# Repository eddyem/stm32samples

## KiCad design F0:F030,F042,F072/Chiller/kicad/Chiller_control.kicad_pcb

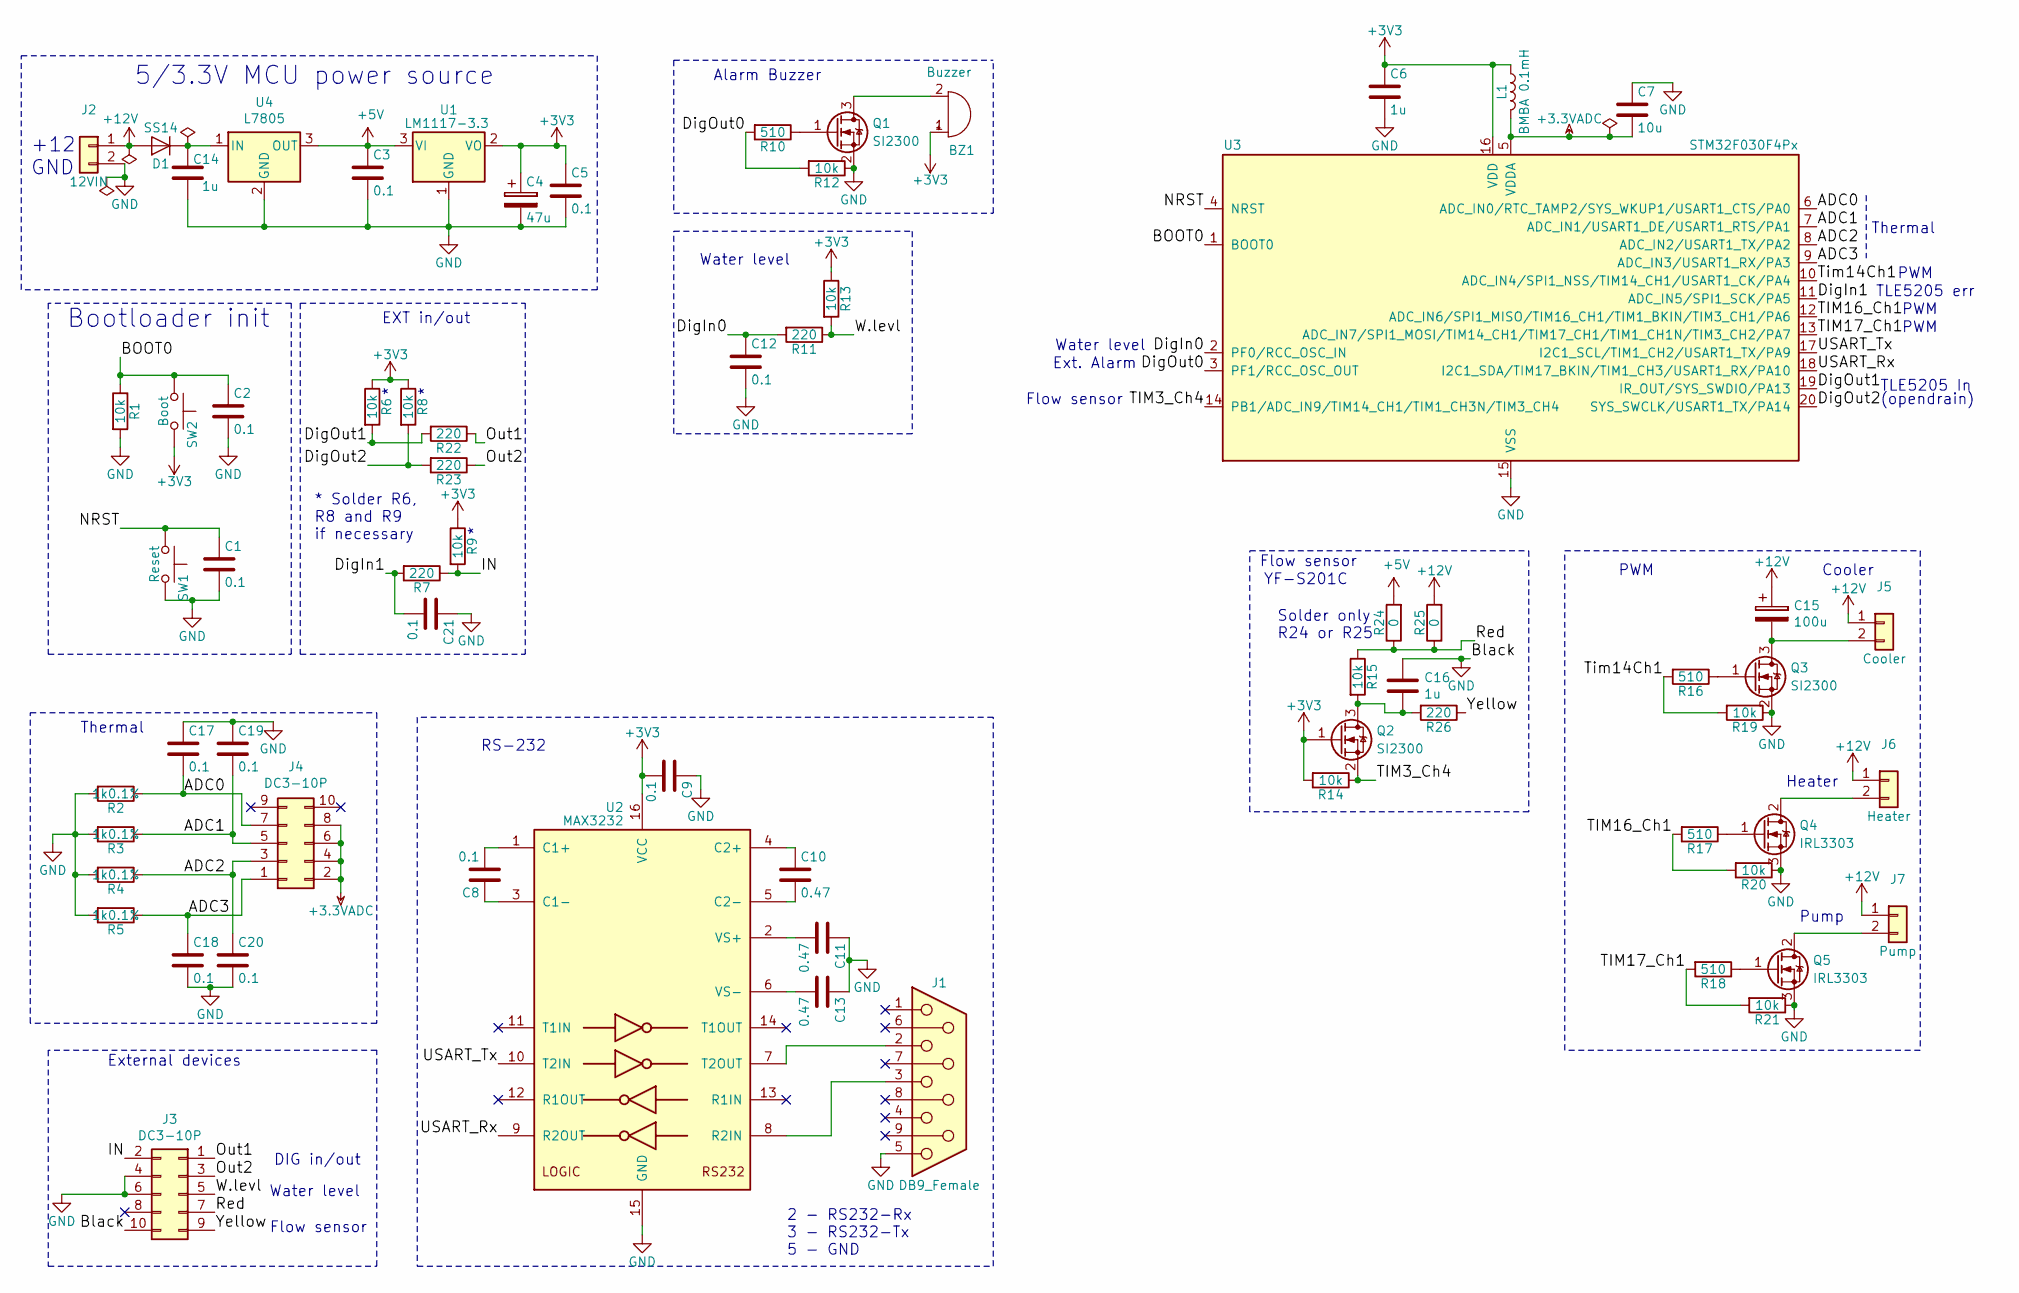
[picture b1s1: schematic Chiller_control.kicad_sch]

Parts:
BZ1: Buzzer; Buzzer_12x9.5RM7.6
C1, C2, C3, C5, C8, C9, C12, C17, C18, C19, C20, C21: 0.1; C_0603_1608Metric_Pad0.99x1.00mm_HandSolder
C4: 47u; CP_Tantalum_Case-A_EIA-3216-18_Hand
C6: 1u; C_0805_HandSoldering
C7: 10u; C_1206_HandSoldering
C10, C11, C13: 0.47; C_0805_HandSoldering
C14, C16: 1u; C_0805_2012Metric_Pad1.29x1.40mm_HandSolder
C15: 100u; CP_Radial_D8.0mm_P3.50mm
D1: SS14; D_SMA_Handsoldering
J1: DB9_Female; DB9-F
J2: 12VIN; TerminalBlock_Pheonix_MKDS1.5-2pol
J3, J4: DC3-10P; IDC-Header_2x05_P2.54mm_Vertical
J5: Cooler; TerminalBlock_Pheonix_MKDS1.5-2pol
J6: Heater; TerminalBlock_Pheonix_MKDS1.5-2pol
J7: Pump; TerminalBlock_Pheonix_MKDS1.5-2pol
L1: BMBA 0.1mH; R_0805_HandSoldering
Q1, Q2, Q3: SI2300; SOT-23_Handsoldering
Q4, Q5: IRL3303; TO-220-3_Vertical
R1, R6, R8, R9, R12, R13, R14, R15, R19, R20, R21: 10k; R_0603_HandSoldering
R2, R3, R4, R5: 1k0.1%; R_0805_HandSoldering
R7, R22, R23, R26: 220; R_0805_2012Metric_Pad1.29x1.40mm_HandSolder
R10, R16, R17, R18: 510; R_0603_HandSoldering
R11: 220; R_0805_HandSoldering
R24, R25: 0; R_0805_2012Metric_Pad1.29x1.40mm_HandSolder
SW1: Reset; SW_SPST_FSMSM
SW2: Boot; SW_SPST_FSMSM
U1: LM1117-3.3; SOT-223
U2: MAX3232; SOIC-16_3.9x9.9mm_Pitch1.27mm
U3: STM32F030F4Px; TSSOP-20_4.4x6.5mm_Pitch0.65mm
U4: L7805; TO-220-3_Vertical

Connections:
+3.3VADC: C7.2, J4.2, J4.4, J4.6, J4.8, L1.2, U3.5 (VDDA)
+3V3: BZ1.1 (+), C4.1, C5.1, C6.1, C9.2, L1.1, Q2.1 (G), R6.1, R8.1, R9.1, R13.1, R14.2, SW2.2, U1.2 (VO), U2.16 (VCC), U3.16 (VDD)
+5V: C3.1, R24.2, U1.3 (VI), U4.3 (OUT)
+12V: C15.1, D1.2 (A), J2.1, J5.1, J6.1, J7.1, R25.2
/ADC0: C17.2, J4.7, R2.1, U3.6 (ADC_IN0/RTC_TAMP2/SYS_WKUP1/USART1_CTS/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)
/ADC1: C19.2, J4.5, R3.1, U3.7 (ADC_IN1/USART1_DE/USART1_RTS/PA1)
/ADC2: C20.1, J4.3, R4.1, U3.8 (ADC_IN2/USART1_TX/PA2)
/ADC3: C18.1, J4.1, R5.1, U3.9 (ADC_IN3/USART1_RX/PA3)
/BOOT0: C2.1, R1.1, SW2.1, U3.1 (BOOT0)
/DigIn0: C12.1, R11.2, U3.2 (PF0/RCC_OSC_IN)
/DigIn1: C21.2, R7.2, U3.11 (ADC_IN5/SPI1_SCK/PA5)
/DigOut0: R10.2, R12.2, U3.3 (PF1/RCC_OSC_OUT)
/DigOut1: R6.2, R22.2, U3.19 (IR_OUT/SYS_SWDIO/PA13)
/DigOut2: R8.2, R23.2, U3.20 (SYS_SWCLK/USART1_TX/PA14)
/IN: J3.2, R7.1, R9.2
/NRST: C1.1, SW1.1, U3.4 (NRST)
/Out1: J3.1, R22.1
/Out2: J3.3, R23.1
/Red: J3.7, R15.1, R24.1, R25.1
/TIM3_Ch4: Q2.2 (S), R14.1, U3.14 (PB1/ADC_IN9/TIM14_CH1/TIM1_CH3N/TIM3_CH4)
/TIM16_Ch1: R17.2, R20.2, U3.12 (ADC_IN6/SPI1_MISO/TIM16_CH1/TIM1_BKIN/T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)
/TIM17_Ch1: R18.2, R21.2, U3.13 (ADC_IN7/SPI1_MOSI/TIM14_CH1/TIM17_CH1/T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)
/Tim14Ch1: R16.2, R19.2, U3.10 (ADC_IN4/SPI1_NSS/TIM14_CH1/USART1_CK/PA4)
/USART_Rx: U2.9 (R2OUT), U3.18 (I2C1_SDA/TIM17_BKIN/TIM1_CH3/USART1_RX/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)
/USART_Tx: U2.10 (T2IN), U3.17 (I2C1_SCL/TIM1_CH2/USART1_TX/PA9)
/W.levl: J3.5, R11.1, R13.2
/Yellow: J3.9, R26.1
GND: C1.2, C2.2, C3.2, C4.2, C5.2, C6.2, C7.1, C9.1, C11.1, C12.2, C13.1, C14.2, C16.1, C17.1, C18.2, C19.1, C20.2, C21.1, J1.5, J2.2, J3.4, J3.6, J3.10, Q1.2 (S), Q3.2 (S), Q4.3 (S), Q5.3 (S), R1.2, R2.2, R3.2, R4.2, R5.2, R12.1, R19.1, R20.1, R21.1, SW1.2, U1.1 (GND), U2.15 (GND), U3.15 (VSS), U4.2 (GND)
unnamed: BZ1.2 (-), Q1.3 (D)
unnamed: C8.1, U2.3 (C1-)
unnamed: C8.2, U2.1 (C1+)
unnamed: C10.1, U2.4 (C2+)
unnamed: C10.2, U2.5 (C2-)
unnamed: C11.2, U2.2 (VS+)
unnamed: C13.2, U2.6 (VS-)
unnamed: C14.1, D1.1 (K), U4.1 (IN)
unnamed: C15.2, J5.2, Q3.3 (D)
unnamed: C16.2, Q2.3 (D), R15.2, R26.2
unnamed: J1.2, U2.7 (T2OUT)
unnamed: J1.3, U2.8 (R2IN)
unnamed: J6.2, Q4.2 (D)
unnamed: J7.2, Q5.2 (D)
unnamed: Q1.1 (G), R10.1
unnamed: Q3.1 (G), R16.1
unnamed: Q4.1 (G), R17.1
unnamed: Q5.1 (G), R18.1

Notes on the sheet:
Thermal
Solder only R24 or R25
Alarm Buzzer
Water level
PWM
+12 GND
Ext. Alarm
Bootloader init
RS-232
EXT in/out
5/3.3V MCU power source
* Solder R6, R8 and R9 if necessary
Cooler
Flow sensor
(opendrain)
DIG in/out
External devices
TLE5205 In
Pump
TLE5205 err
2 - RS232-Rx 3 - RS232-Tx 5 - GND
YF-S201C
Heater

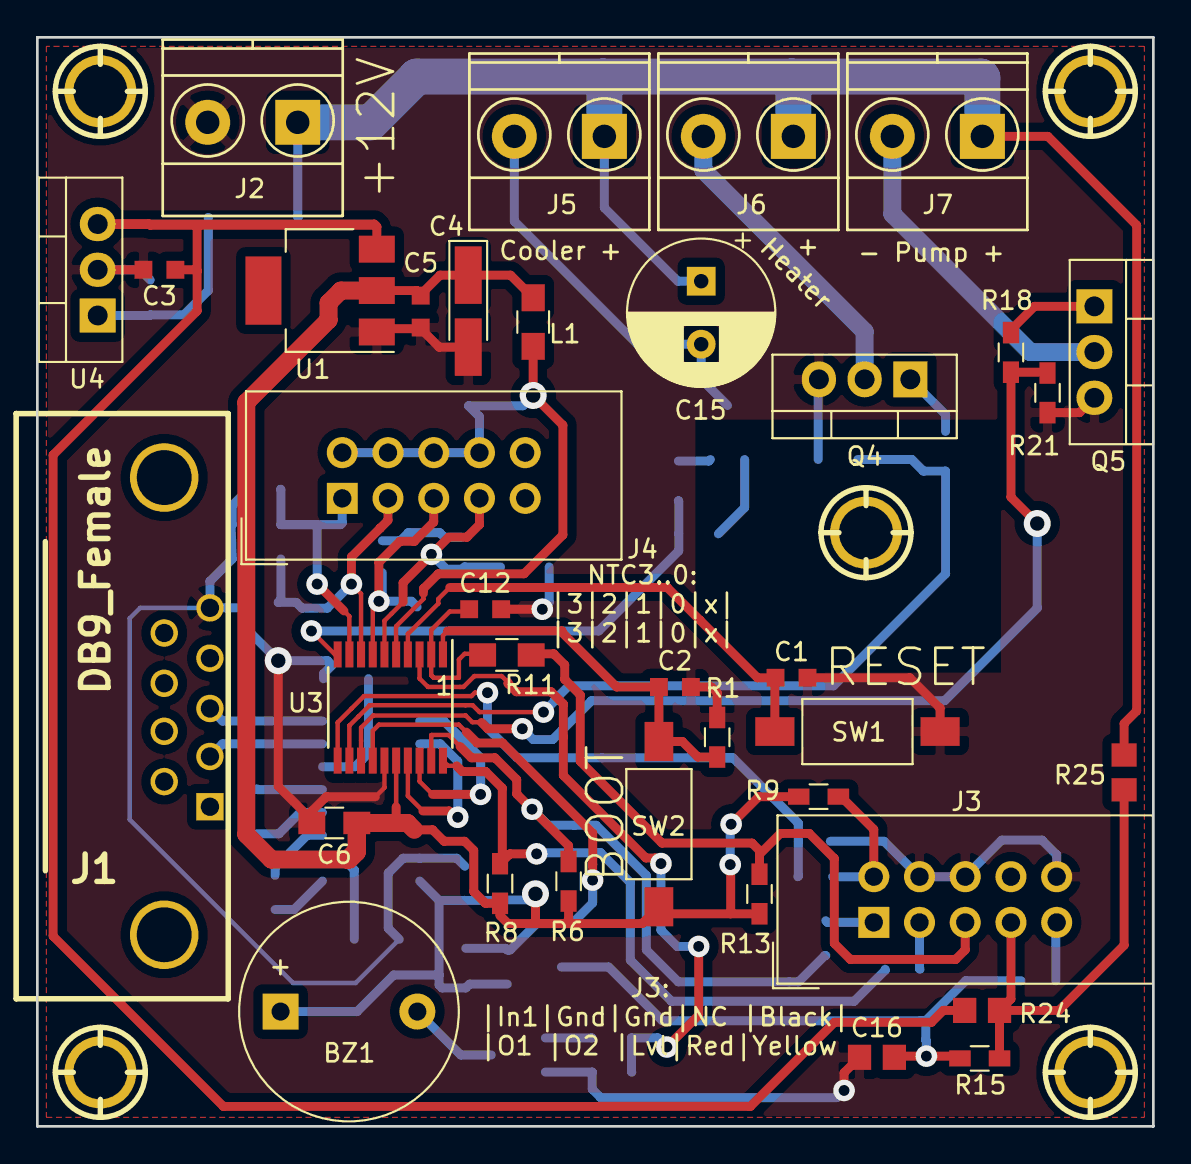
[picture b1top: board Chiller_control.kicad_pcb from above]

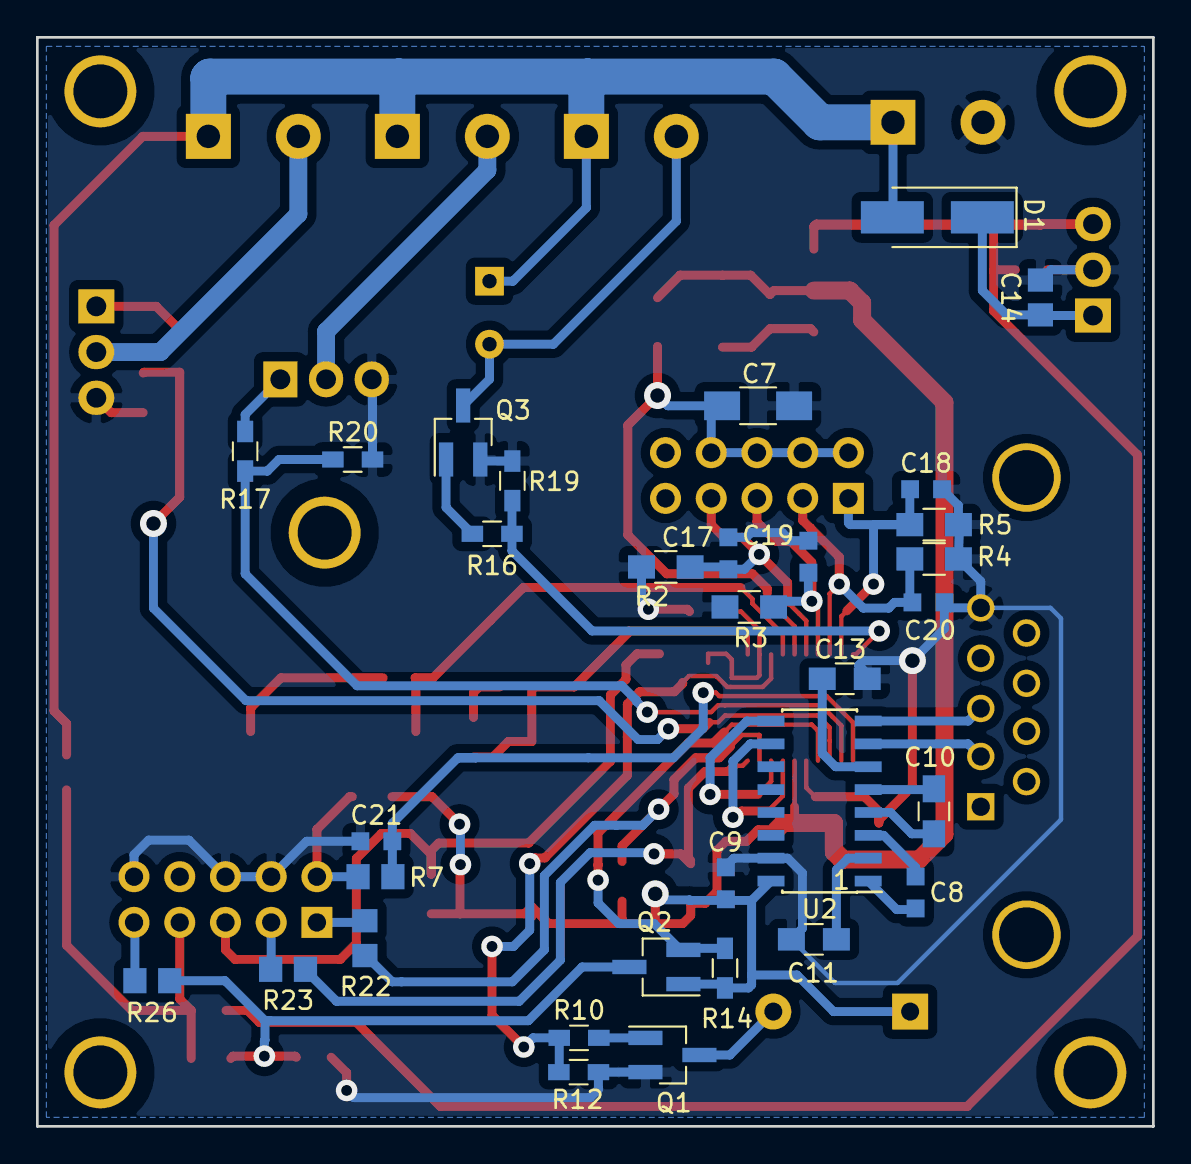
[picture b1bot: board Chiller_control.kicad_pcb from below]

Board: 2 copper layers, 62.0 x 60.5 mm, 73 parts (32 on the bottom side), 46 nets.

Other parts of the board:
hole_3mm, hole_3mm#2, hole_3mm#3, hole_3mm#4, hole_3mm#5: Val**; hole_3mm

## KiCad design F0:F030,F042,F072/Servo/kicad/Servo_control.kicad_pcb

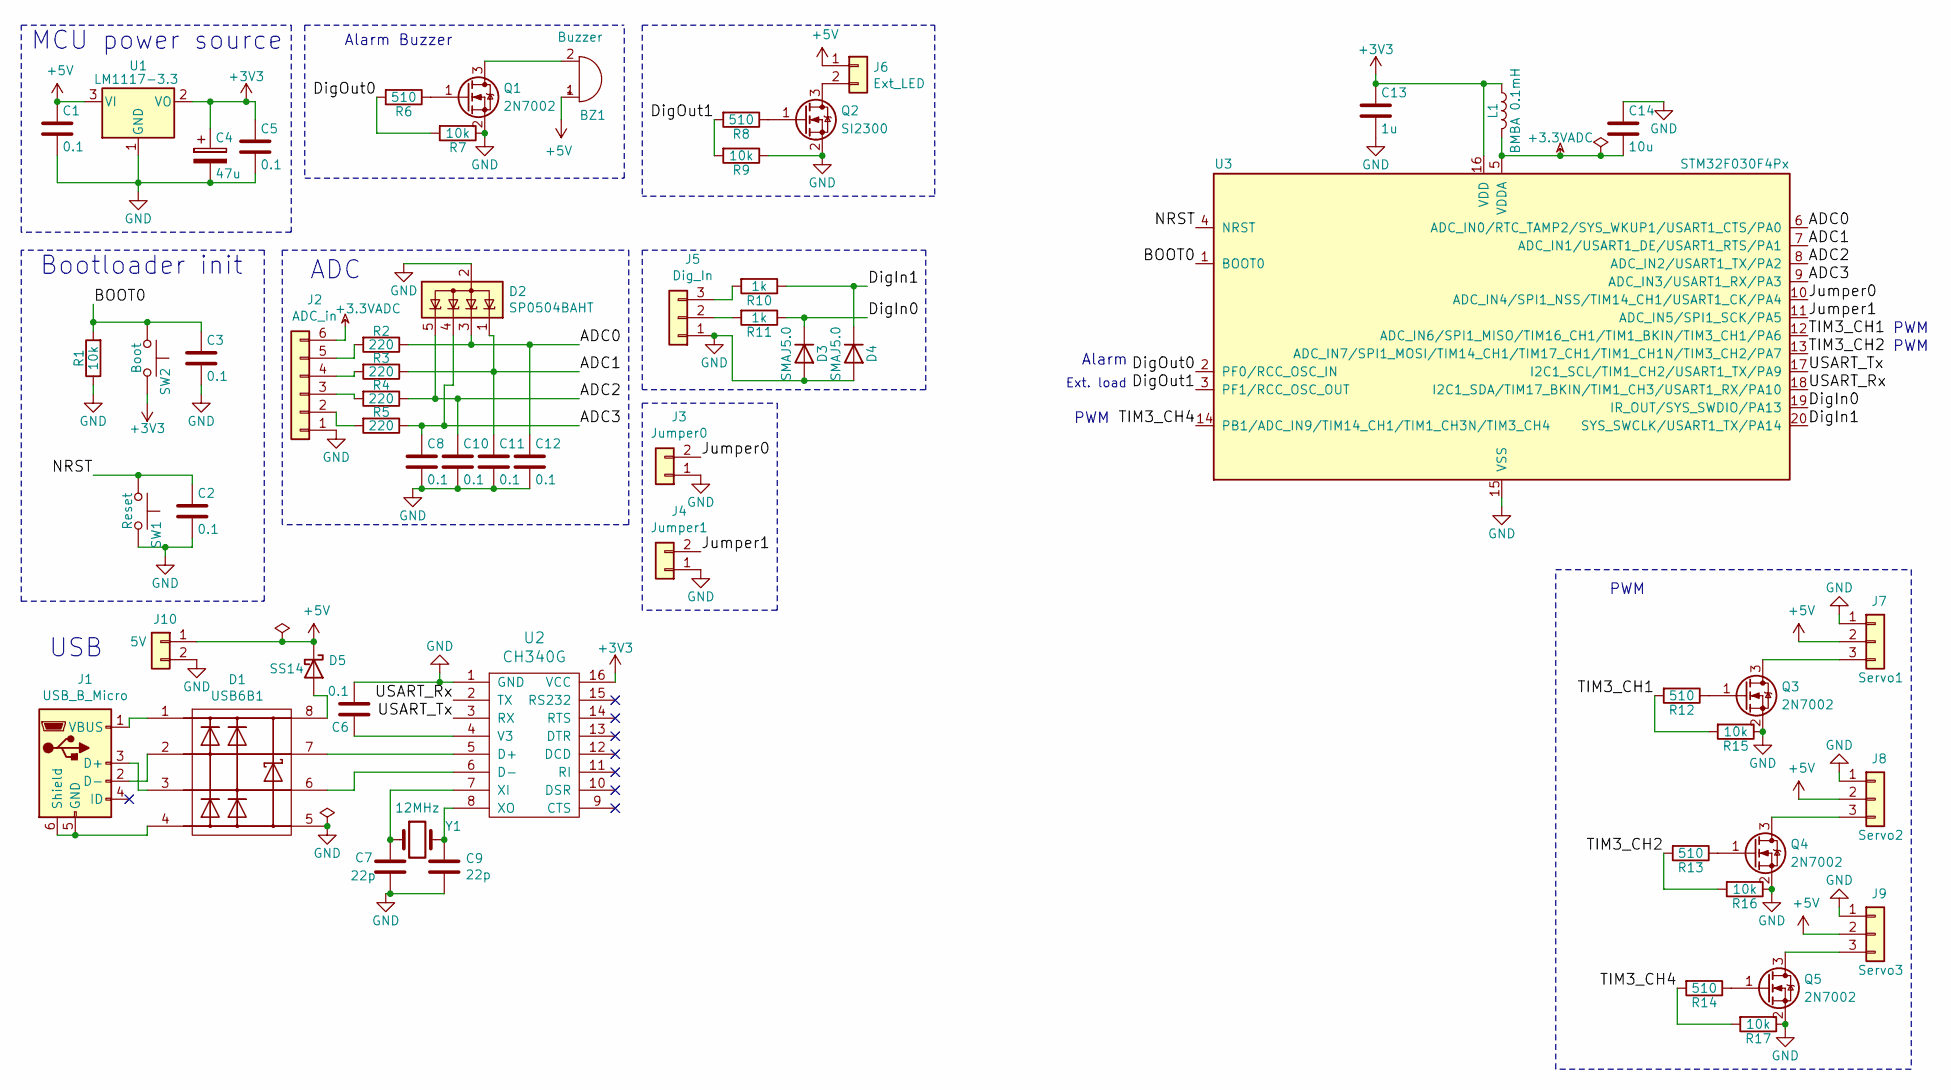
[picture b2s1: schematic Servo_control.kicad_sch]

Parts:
BZ1: Buzzer; Buzzer_12x9.5RM7.6
C1, C2, C3, C5, C6, C8, C10, C11, C12: 0.1; C_0603_1608Metric_Pad0.84x1.00mm_HandSolder
C4: 47u; CP_EIA-3216-18_Kemet-A_Pad1.53x1.40mm_HandSolder
C7, C9: 22p; C_0603_1608Metric_Pad0.84x1.00mm_HandSolder
C13: 1u; C_0805_2012Metric_Pad1.15x1.50mm_HandSolder
C14: 10u; C_1206_3216Metric_Pad1.24x1.80mm_HandSolder
D1: USB6B1; SOIC-8_3.9x4.9mm_P1.27mm
D2: SP0504BAHT; SOT-23-5
D3, D4: SMAJ5.0; D_SMA_Handsoldering
D5: SS14; D_SMA_Handsoldering
J1: USB_B_Micro; USB_Micro-B_Wuerth-629105150521
J2: ADC_in; PinHeader_1x06_P2.54mm_Vertical
J3: Jumper0; PinHeader_1x02_P2.54mm_Vertical
J4: Jumper1; PinHeader_1x02_P2.54mm_Vertical
J5: Dig_In; PinHeader_1x03_P2.54mm_Vertical
J6: Ext_LED; PinHeader_1x02_P2.54mm_Vertical
J7: Servo1; PinHeader_1x03_P2.54mm_Vertical
J8: Servo2; PinHeader_1x03_P2.54mm_Vertical
J9: Servo3; PinHeader_1x03_P2.54mm_Vertical
J10: 5V; PinHeader_1x02_P2.54mm_Vertical
L1: BMBA 0.1mH; L_0805_2012Metric_Pad1.15x1.50mm_HandSolder
Q1, Q3, Q4, Q5: 2N7002; SOT-23
Q2: SI2300; SOT-23
R1, R7, R9, R15, R16, R17: 10k; R_0805_2012Metric_Pad1.15x1.50mm_HandSolder
R2, R3, R4, R5: 220; R_0805_2012Metric_Pad1.15x1.50mm_HandSolder
R6, R8, R12, R13, R14: 510; R_0805_2012Metric_Pad1.15x1.50mm_HandSolder
R10, R11: 1k; R_0805_2012Metric_Pad1.15x1.50mm_HandSolder
SW1: Reset; SW_SPST_FSMSM
SW2: Boot; SW_SPST_FSMSM
U1: LM1117-3.3; SOT-223-3_TabPin2
U2: CH340G; SOIC-16_3.9x9.9mm_P1.27mm
U3: STM32F030F4Px; TSSOP-20_4.4x6.5mm_P0.65mm
Y1: 12MHz; Crystal_HC49-U_Vertical

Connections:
+3.3VADC: C14.2, J2.6, L1.2, U3.5 (VDDA)
+3V3: C4.1, C5.1, C13.1, L1.1, SW2.2, U1.2 (VO), U2.16 (VCC), U3.16 (VDD)
+5V: BZ1.1 (+), C1.1, D5.1 (K), J6.1, J7.2, J8.2, J9.2, J10.1, U1.3 (VI)
/ADC0: C12.1, D2.3 (K), R2.1, U3.6 (ADC_IN0/RTC_TAMP2/SYS_WKUP1/USART1_CTS/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)
/ADC1: C11.1, D2.1 (K), R3.1, U3.7 (ADC_IN1/USART1_DE/USART1_RTS/PA1)
/ADC2: C10.1, D2.5 (K), R4.1, U3.8 (ADC_IN2/USART1_TX/PA2)
/ADC3: C8.1, D2.4 (K), R5.1, U3.9 (ADC_IN3/USART1_RX/PA3)
/BOOT0: C3.1, R1.2, SW2.1, U3.1 (BOOT0)
/DigIn0: D3.1 (K), R11.1, U3.19 (IR_OUT/SYS_SWDIO/PA13)
/DigIn1: D4.1 (K), R10.1, U3.20 (SYS_SWCLK/USART1_TX/PA14)
/DigOut0: R6.2, R7.2, U3.2 (PF0/RCC_OSC_IN)
/DigOut1: R8.2, R9.2, U3.3 (PF1/RCC_OSC_OUT)
/Jumper0: J3.2, U3.10 (ADC_IN4/SPI1_NSS/TIM14_CH1/USART1_CK/PA4)
/Jumper1: J4.2, U3.11 (ADC_IN5/SPI1_SCK/PA5)
/NRST: C2.1, SW1.1, U3.4 (NRST)
/TIM3_CH1: R12.2, R15.2, U3.12 (ADC_IN6/SPI1_MISO/TIM16_CH1/TIM1_BKIN/T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)
/TIM3_CH2: R13.2, R16.2, U3.13 (ADC_IN7/SPI1_MOSI/TIM14_CH1/TIM17_CH1/T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)
/TIM3_CH4: R14.2, R17.2, U3.14 (PB1/ADC_IN9/TIM14_CH1/TIM1_CH3N/TIM3_CH4)
/USART_Rx: U2.2 (TX), U3.18 (I2C1_SDA/TIM17_BKIN/TIM1_CH3/USART1_RX/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)
/USART_Tx: U2.3 (RX), U3.17 (I2C1_SCL/TIM1_CH2/USART1_TX/PA9)
GND: C1.2, C2.2, C3.2, C4.2, C5.2, C6.2, C7.2, C8.2, C9.2, C10.2, C11.2, C12.2, C13.2, C14.1, D1.5 (GND), D2.2 (A), D3.2 (A), D4.2 (A), J2.1, J3.1, J4.1, J5.1, J7.1, J8.1, J9.1, J10.2, Q1.2 (S), Q2.2 (S), Q3.2 (S), Q4.2 (S), Q5.2 (S), R1.1, R7.1, R9.1, R15.1, R16.1, R17.1, SW1.2, U1.1 (GND), U2.1 (GND), U3.15 (VSS)
unnamed: BZ1.2 (-), Q1.3 (D)
unnamed: C6.1, U2.4 (V3)
unnamed: C7.1, U2.7 (XI), Y1.1
unnamed: C9.1, U2.8 (XO), Y1.2
unnamed: D1.1 (VCC), J1.1 (VBUS)
unnamed: D1.2 (I/O1), J1.2 (D-)
unnamed: D1.3 (I/O2), J1.3 (D+)
unnamed: D1.4 (GND), J1.5 (GND), J1.6 (Shield)
unnamed: D1.6 (I/O2), U2.6 (D-)
unnamed: D1.7 (I/O1), U2.5 (D+)
unnamed: D1.8 (VCC), D5.2 (A)
unnamed: J2.2, R5.2
unnamed: J2.3, R4.2
unnamed: J2.4, R3.2
unnamed: J2.5, R2.2
unnamed: J5.2, R11.2
unnamed: J5.3, R10.2
unnamed: J6.2, Q2.3 (D)
unnamed: J7.3, Q3.3 (D)
unnamed: J8.3, Q4.3 (D)
unnamed: J9.3, Q5.3 (D)
unnamed: Q1.1 (G), R6.1
unnamed: Q2.1 (G), R8.1
unnamed: Q3.1 (G), R12.1
unnamed: Q4.1 (G), R13.1
unnamed: Q5.1 (G), R14.1

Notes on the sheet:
Ext. load
PWM
ADC
USB
Alarm Buzzer
MCU power source
Bootloader init
Alarm

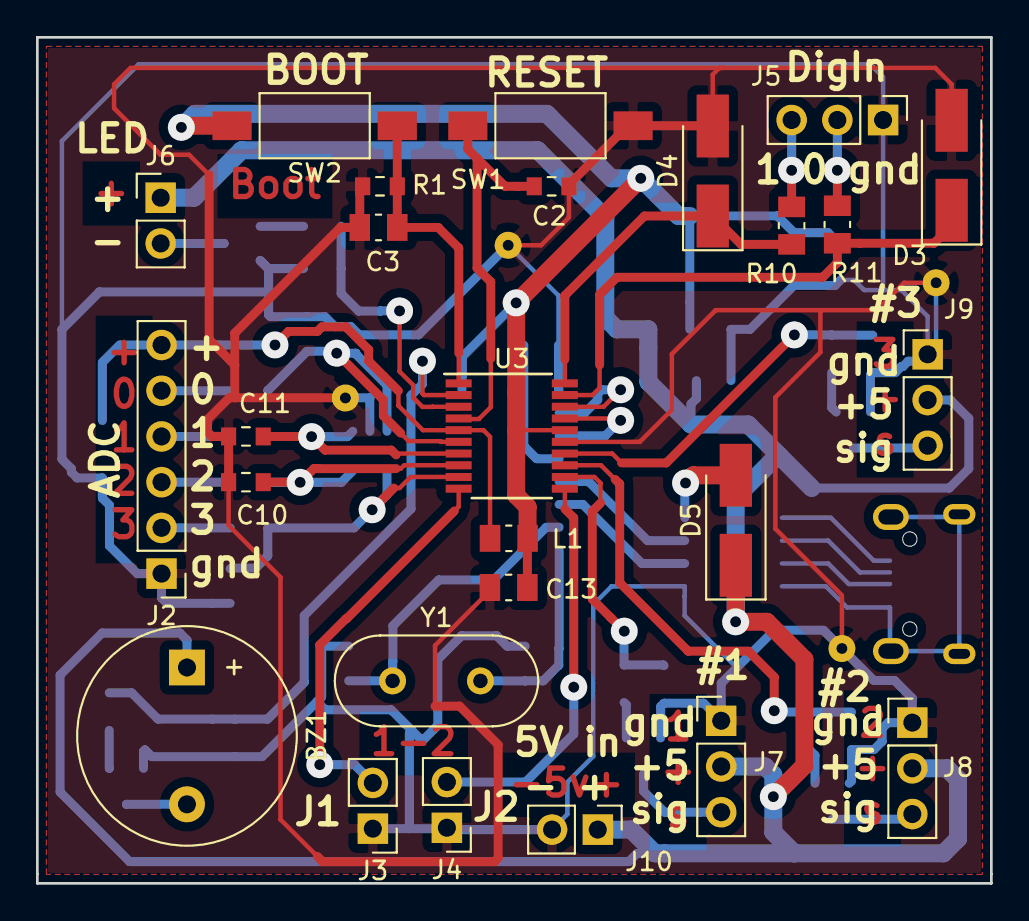
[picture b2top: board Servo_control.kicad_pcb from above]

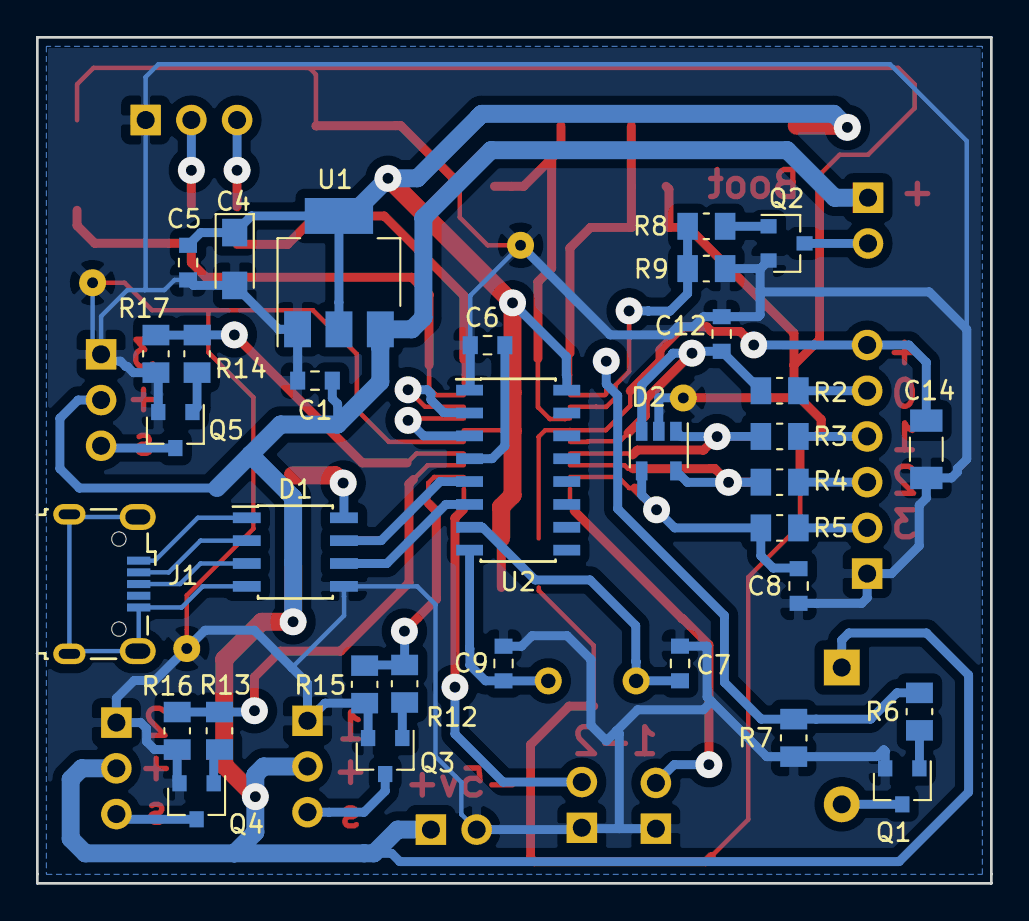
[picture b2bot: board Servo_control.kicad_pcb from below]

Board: 2 copper layers, 53.0 x 47.0 mm, 59 parts (33 on the bottom side), 47 nets.

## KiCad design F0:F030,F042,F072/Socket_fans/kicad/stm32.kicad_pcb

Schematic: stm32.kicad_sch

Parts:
C1, C2, C3, C4, C5, C6, C8, C13, C14, C15, C16, C17, C18, C19, C20: 0.1; C_0603_1608Metric_Pad1.05x0.95mm_HandSolder
C7: 47uF, 10V; CP_EIA-6032-28_Kemet-C_Pad2.25x2.35mm_HandSolder
C9: 10uF, 10V; C_1206_3216Metric_Pad1.42x1.75mm_HandSolder
C10: 47u, 25V; CP_Radial_D8.0mm_P3.50mm
D1, D2, D4, D5, D6, D9: 1N5819; D_SOD-323_HandSoldering
D3: MM3Z7V5; D_0805_2012Metric_Pad1.15x1.40mm_HandSolder
D7: MM3Z4V3; D_0805_2012Metric_Pad1.15x1.40mm_HandSolder
D8, D10: MM3Z3V6; D_0805_2012Metric_Pad1.15x1.40mm_HandSolder
J1: 12VIN; TerminalBlock_Phoenix_MKDS-1,5-2_1x02_P5.00mm_Horizontal
J2: thermal; PinSocket_2x04_P2.54mm_Vertical
J3: Buzzer; JST_EH_B2B-EH-A_1x02_P2.50mm_Vertical
J4: cooler3; JST_EH_B2B-EH-A_1x02_P2.50mm_Vertical
J5, J6: FAN; FanPinHeader_1x04_P2.54mm_Vertical
J7, J10: Conn_01x02_Female; PinSocket_1x02_P2.54mm_Vertical
J8: MKDS; TerminalBlock_Phoenix_MKDS-1,5-2_1x02_P5.00mm_Horizontal
K1: SRD-12VDC; Relay_SPDT_SANYOU_SRD_Series_Form_C
L1: BMBA 0.1mH; L_0805_2012Metric_Pad1.15x1.40mm_HandSolder
P1: USB_A; USB_B_OST_USB-B1HSxx_Horizontal
P2, P3, P4, P5: Hole; MountingHole_3.2mm_M3
Q1: AO3401; SOT-23_Handsoldering
Q2, Q3, Q4, Q5, Q6: IRLML2502; SOT-23_Handsoldering
R1, R2, R4, R6, R8, R13, R14, R16, R17, R34: 10k; R_0603_1608Metric_Pad1.05x0.95mm_HandSolder
R3, R5, R7, R9: 4k7, 1%; R_0805_2012Metric_Pad1.15x1.40mm_HandSolder
R10, R11, R12, R15, R18, R19, R20, R21, R24, R25, R32: 510; R_0603_1608Metric_Pad1.05x0.95mm_HandSolder
R22: 47k; R_0603_1608Metric_Pad1.05x0.95mm_HandSolder
R23, R30, R31: 22; R_0603_1608Metric_Pad1.05x0.95mm_HandSolder
R26: 3.3k; R_0603_1608Metric_Pad1.05x0.95mm_HandSolder
R27: 1k; R_0603_1608Metric_Pad1.05x0.95mm_HandSolder
R28, R29: 4.7k; R_0603_1608Metric_Pad1.05x0.95mm_HandSolder
SW1, SW2: SW_Push; PinSocket_1x02_P2.54mm_Vertical
U1: LM1117-3.3; SOT-223-3_TabPin2
U2: L7805; TO-220-3_Vertical
U3: STM32F072CBTx; LQFP-48_7x7mm_P0.5mm
U4: USBLC6-2SC6; SOT-23-6

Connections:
+5V: D1.1 (K), D2.1 (K), R28.1, U1.3
+12V: C3.1, C10.1, D3.1 (K), D4.1 (K), D5.1 (K), D6.1 (K), D9.1 (K), J3.2, J4.1, J5.2, J6.2, K1.2, Q1.2 (S), R26.1, U2.1 (IN)
/5Vin: C8.1, C9.1, D1.2 (A), U2.3 (OUT)
/5Vusb: D2.2 (A), P1.1 (VBUS), U4.5 (VBUS)
/ADC0: C1.2, R2.2, U3.10 (PA0)
/ADC1: C2.2, R4.2, U3.11 (PA1)
/ADC2: C4.2, R6.2, U3.12 (PA2)
/ADC3: C5.2, R8.2, U3.13 (PA3)
/AIN0: C16.1, D7.1 (K), R26.2, R27.1, U3.14 (PA4)
/AIN1: C18.1, R28.2, R29.1, U3.15 (PA5)
/BOOT0: J7.2, R22.1, U3.44 (BOOT0)
/Btn0: R24.1, U3.27 (PB14)
/Btn1: R25.1, U3.28 (PB15)
/Buzzer: R12.2, R16.2, U3.37 (PA14)
/Cooler0: R11.2, R14.2, U3.40 (PB4)
/Cooler1: R10.2, R13.2, U3.41 (PB5)
/NRST: J10.1, U3.7 (NRST)
/Relay: R32.2, R34.1, U3.2 (PC13)
/TIM1_CH1: R21.1, U3.29 (PA8)
/TIM1_CH2: R20.1, U3.30 (PA9)
/TIM1_CH3: R15.2, R17.2, U3.31 (PA10)
/TIM3_CH1: D10.1 (K), R19.1, U3.16 (PA6)
/TIM14_CH1: D8.1 (K), R18.1, U3.17 (PA7)
GND: C1.1, C2.1, C3.2, C4.1, C5.1, C6.2, C7.2, C8.2, C9.2, C10.2, C13.2, C14.2, C15.1, C16.2, C17.1, C18.2, C19.1, C20.2, D7.2 (A), D8.2 (A), D10.2 (A), J1.2, J10.2, P1.4 (GND), P1.5 (Shield), Q2.2 (S), Q3.2 (S), Q4.2 (S), Q5.2 (S), Q6.2 (S), R1.2, R3.1, R5.1, R7.1, R9.1, R13.1, R14.1, R16.1, R17.1, R22.2, R27.2, R29.2, R34.2, SW1.1, SW2.1, U1.1, U2.2 (GND), U3.8 (VSSA), U3.23 (VSS), U3.35 (VSS), U3.47 (VSS), U4.2 (GND)
unnamed: C13.1, R24.2, SW1.2
unnamed: C14.1, R25.2, SW2.2
unnamed: D3.2 (A), Q1.1 (G), R1.1
unnamed: D4.2 (A), J5.1, Q2.3 (D)
unnamed: D5.2 (A), J6.1, Q3.3 (D)
unnamed: D6.2 (A), J4.2, Q5.3 (D)
unnamed: D9.2 (A), K1.5, Q6.3 (D)
unnamed: J1.1, Q1.3 (D)
unnamed: J2.1, R8.1, R9.2
unnamed: J2.3, R6.1, R7.2
unnamed: J2.5, R4.1, R5.2
unnamed: J2.7, R2.1, R3.2
unnamed: J3.1, Q4.3 (D)
unnamed: J5.3, R18.2
unnamed: J5.4, R20.2
unnamed: J6.3, R19.2
unnamed: J6.4, R21.2
unnamed: J7.1, R23.1
unnamed: J8.1, K1.1
unnamed: J8.2, K1.3
unnamed: P1.2 (D-), U4.4 (I/O2)
unnamed: P1.3 (D+), U4.6 (I/O1)
unnamed: Q2.1 (G), R10.1
unnamed: Q3.1 (G), R11.1
unnamed: Q4.1 (G), R12.1
unnamed: Q5.1 (G), R15.1
unnamed: Q6.1 (G), R32.1
unnamed: R30.1, U4.3 (I/O2)
unnamed: R30.2, U3.32 (PA11)
unnamed: R31.1, U4.1 (I/O1)
unnamed: R31.2, U3.33 (PA12)

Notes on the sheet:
Cooler channels
ADC block (voltage)
V12 = 12Vin/4.3
+12 GND
3.3V MCU power source
External 12V voltage control
External 5V voltage control
Boot, reset
VCC BOOT0 NRST GND
5V power source
Alarm Buzzer
Thermal
V5 = U5/2

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
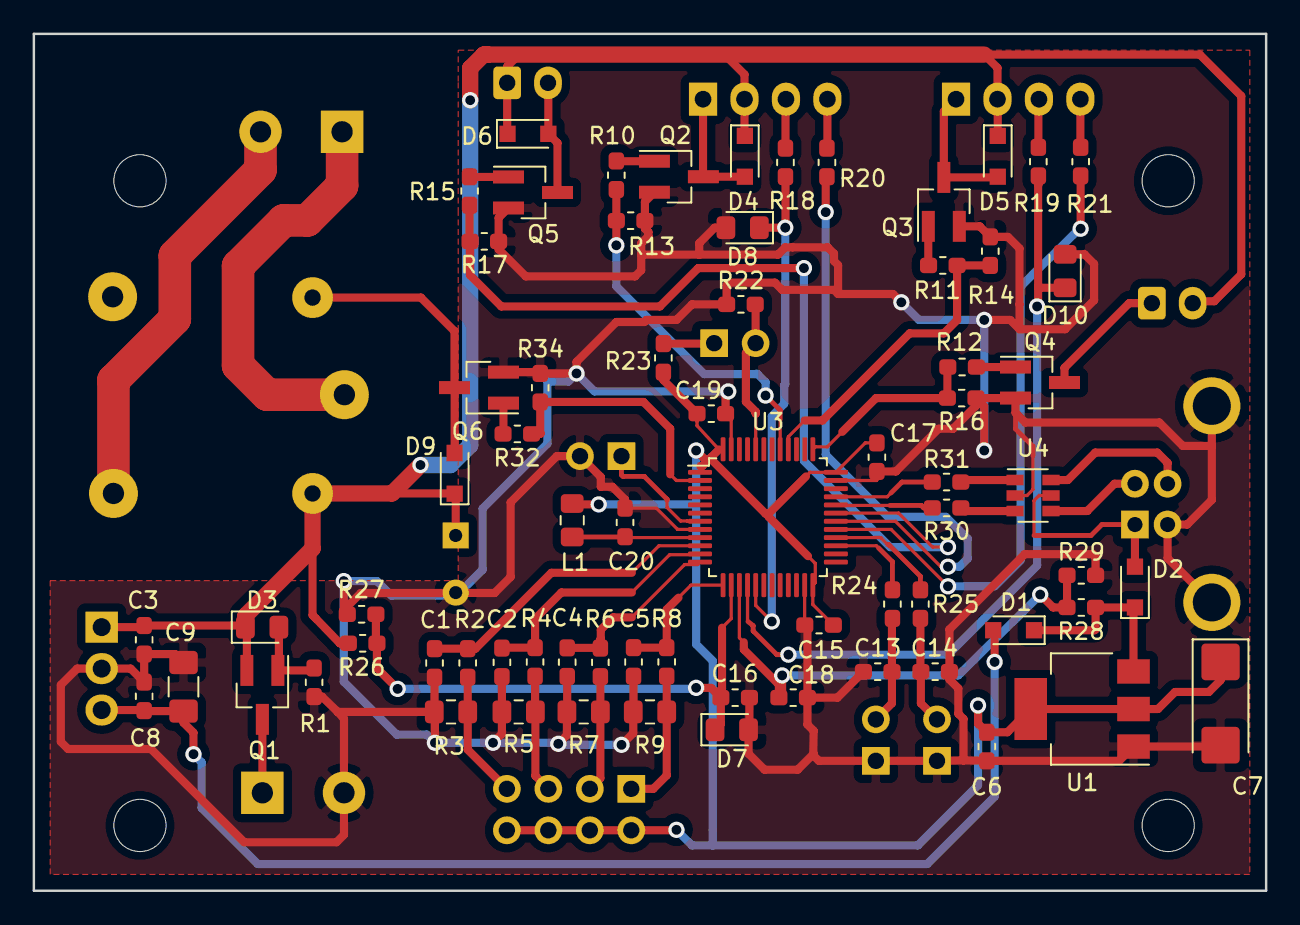
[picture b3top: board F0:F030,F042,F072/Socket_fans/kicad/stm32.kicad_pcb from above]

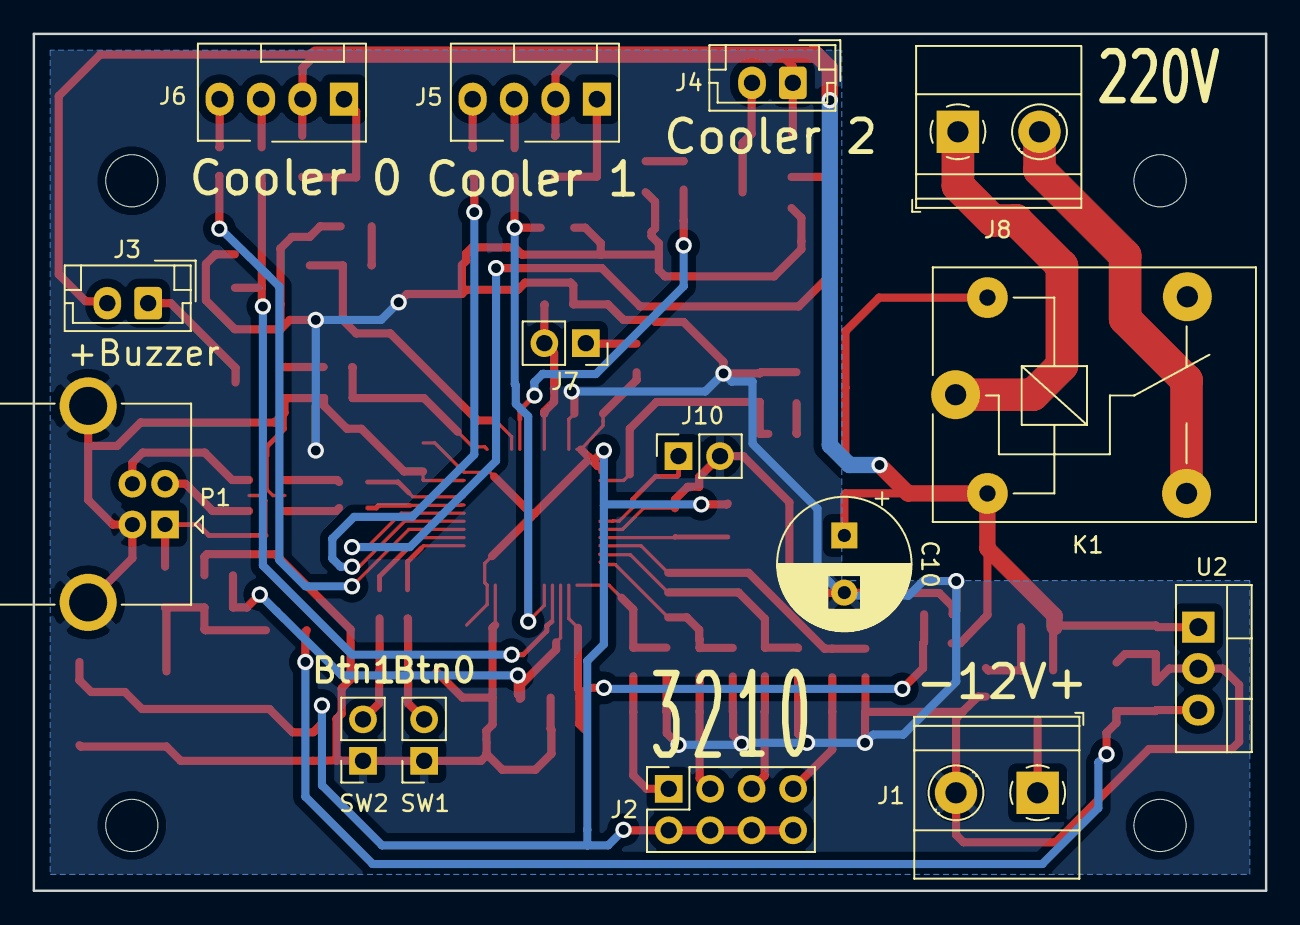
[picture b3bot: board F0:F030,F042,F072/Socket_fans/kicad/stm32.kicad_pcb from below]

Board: 2 copper layers, 75.5 x 52.5 mm, 89 parts (15 on the bottom side), 57 nets.
